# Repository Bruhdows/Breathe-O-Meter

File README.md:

# Breathe-O-Meter

Breathe-O-Meter is a small desktop hardware project for Hack Club Fallout. It measures room temperature, humidity, and air pressure, then shows the data on a built-in screen.

Since it will usually sit plugged into a computer, I also want it to work as a tiny desk companion with a few buttons for simple macro/macropad actions (maybe some knobs aswell?).

## Features

- Temperature, humidity, and pressure sensing
- Built-in display for live room readings
- Comfort/status indicator
- Programmable buttons for simple macros
- USB-powered desktop design

## Hardware

The project will use an ESP32 or ESP32-S3, a BME280 environmental sensor, a larger (3-4 inch?) display, and several keys.

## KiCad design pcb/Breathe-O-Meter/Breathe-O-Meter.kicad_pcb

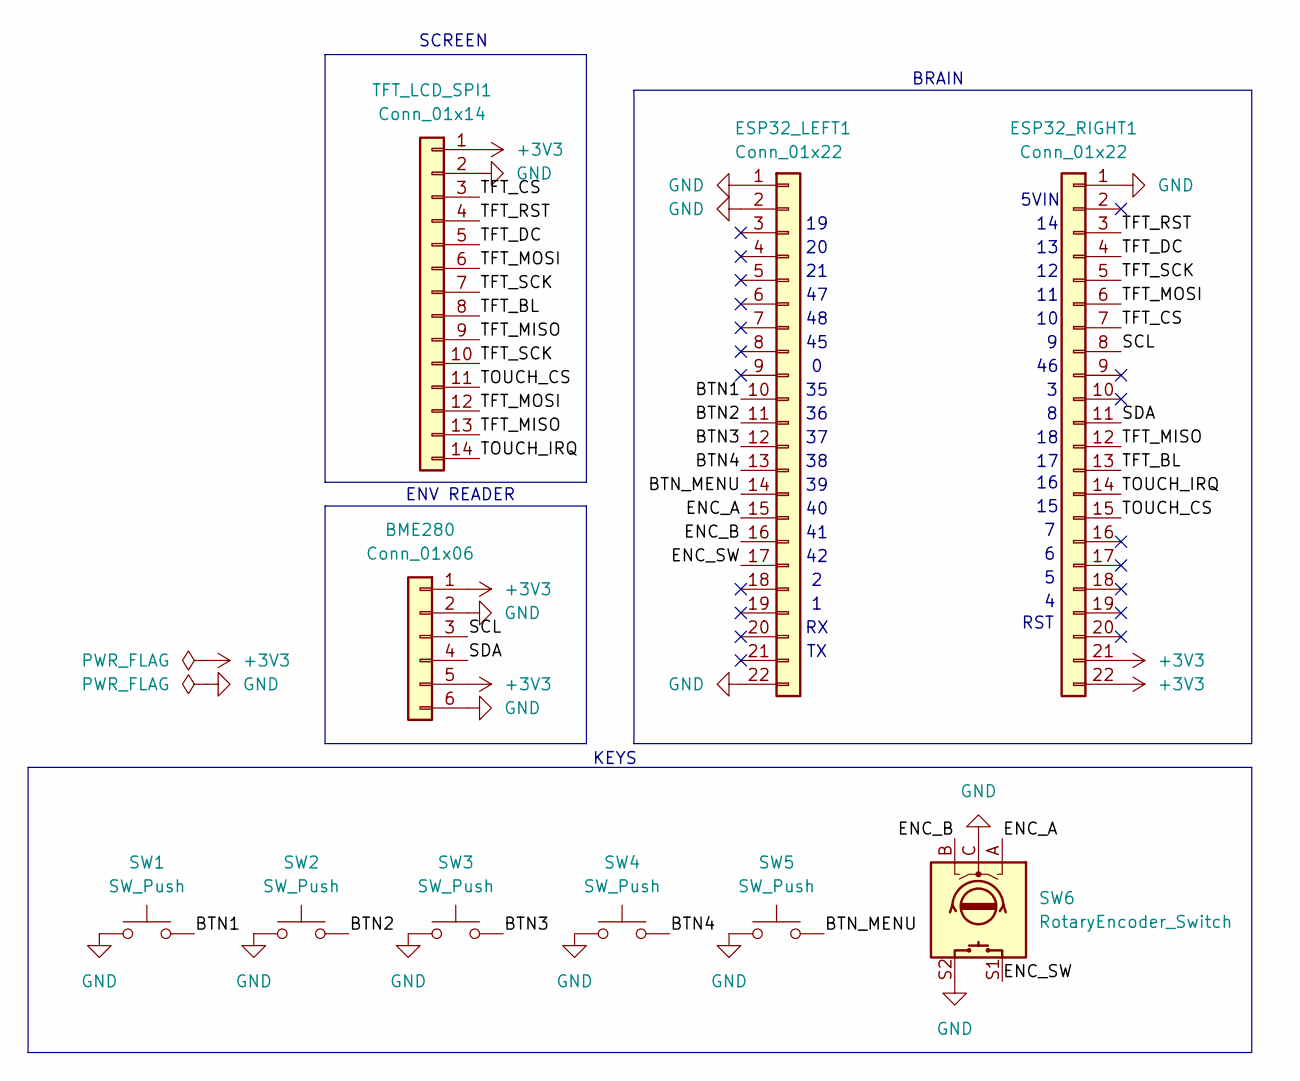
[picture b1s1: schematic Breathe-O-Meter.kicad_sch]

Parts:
BME280: Conn_01x06; PinSocket_1x06_P2.54mm_Vertical
ESP32_LEFT1, ESP32_RIGHT1: Conn_01x22; PinSocket_1x22_P2.54mm_Vertical
SW1, SW2, SW3, SW4, SW5: SW_Push; SW_Hotswap_Kailh_Choc_V1
SW6: RotaryEncoder_Switch; RotaryEncoder_Alps_EC12E-Switch_Vertical_H20mm
TFT_LCD_SPI1: Conn_01x14; PinSocket_1x14_P2.54mm_Vertical

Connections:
+3V3: BME280.1, BME280.5, ESP32_RIGHT1.21, ESP32_RIGHT1.22, TFT_LCD_SPI1.1
/BTN1: ESP32_LEFT1.10, SW1.2
/BTN2: ESP32_LEFT1.11, SW2.2
/BTN3: ESP32_LEFT1.12, SW3.2
/BTN4: ESP32_LEFT1.13, SW4.2
/BTN_MENU: ESP32_LEFT1.14, SW5.2
/ENC_A: ESP32_LEFT1.15, SW6.A
/ENC_B: ESP32_LEFT1.16, SW6.B
/ENC_SW: ESP32_LEFT1.17, SW6.S1
/SCL: BME280.3, ESP32_RIGHT1.8
/SDA: BME280.4, ESP32_RIGHT1.11
/TFT_BL: ESP32_RIGHT1.13, TFT_LCD_SPI1.8
/TFT_CS: ESP32_RIGHT1.7, TFT_LCD_SPI1.3
/TFT_DC: ESP32_RIGHT1.4, TFT_LCD_SPI1.5
/TFT_MISO: ESP32_RIGHT1.12, TFT_LCD_SPI1.9, TFT_LCD_SPI1.13
/TFT_MOSI: ESP32_RIGHT1.6, TFT_LCD_SPI1.6, TFT_LCD_SPI1.12
/TFT_RST: ESP32_RIGHT1.3, TFT_LCD_SPI1.4
/TFT_SCK: ESP32_RIGHT1.5, TFT_LCD_SPI1.7, TFT_LCD_SPI1.10
/TOUCH_CS: ESP32_RIGHT1.15, TFT_LCD_SPI1.11
/TOUCH_IRQ: ESP32_RIGHT1.14, TFT_LCD_SPI1.14
GND: BME280.2, BME280.6, ESP32_LEFT1.1, ESP32_LEFT1.2, ESP32_LEFT1.22, ESP32_RIGHT1.1, SW1.1, SW2.1, SW3.1, SW4.1, SW5.1, SW6.C, SW6.S2, TFT_LCD_SPI1.2

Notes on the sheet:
RST
SCREEN
ENV READER
5VIN
BRAIN
KEYS

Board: 2 copper layers, 10 parts (0 on the bottom side), 21 nets, no tracks yet.

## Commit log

2026-05-05 Prepare repo
2026-05-06 Started work on PCB schem + .gitignore for backups
